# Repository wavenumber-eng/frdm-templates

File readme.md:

# FRDM MCX Templates

- Designs are now current edited in Altium, then imported into KiCad

- Always double check pin header IO assignments, mechanicals.  This template was created using the latest available documentation at the time of their creation. Reasonable efforts were made to ensure mechanical/electrical accuracy.   

- These templates are distributed in the hope that it will be useful, but WITHOUT ANY WARRANTY; without even the implied warranty of MERCHANTABILITY or FITNESS FOR A PARTICULAR PURPOSE.

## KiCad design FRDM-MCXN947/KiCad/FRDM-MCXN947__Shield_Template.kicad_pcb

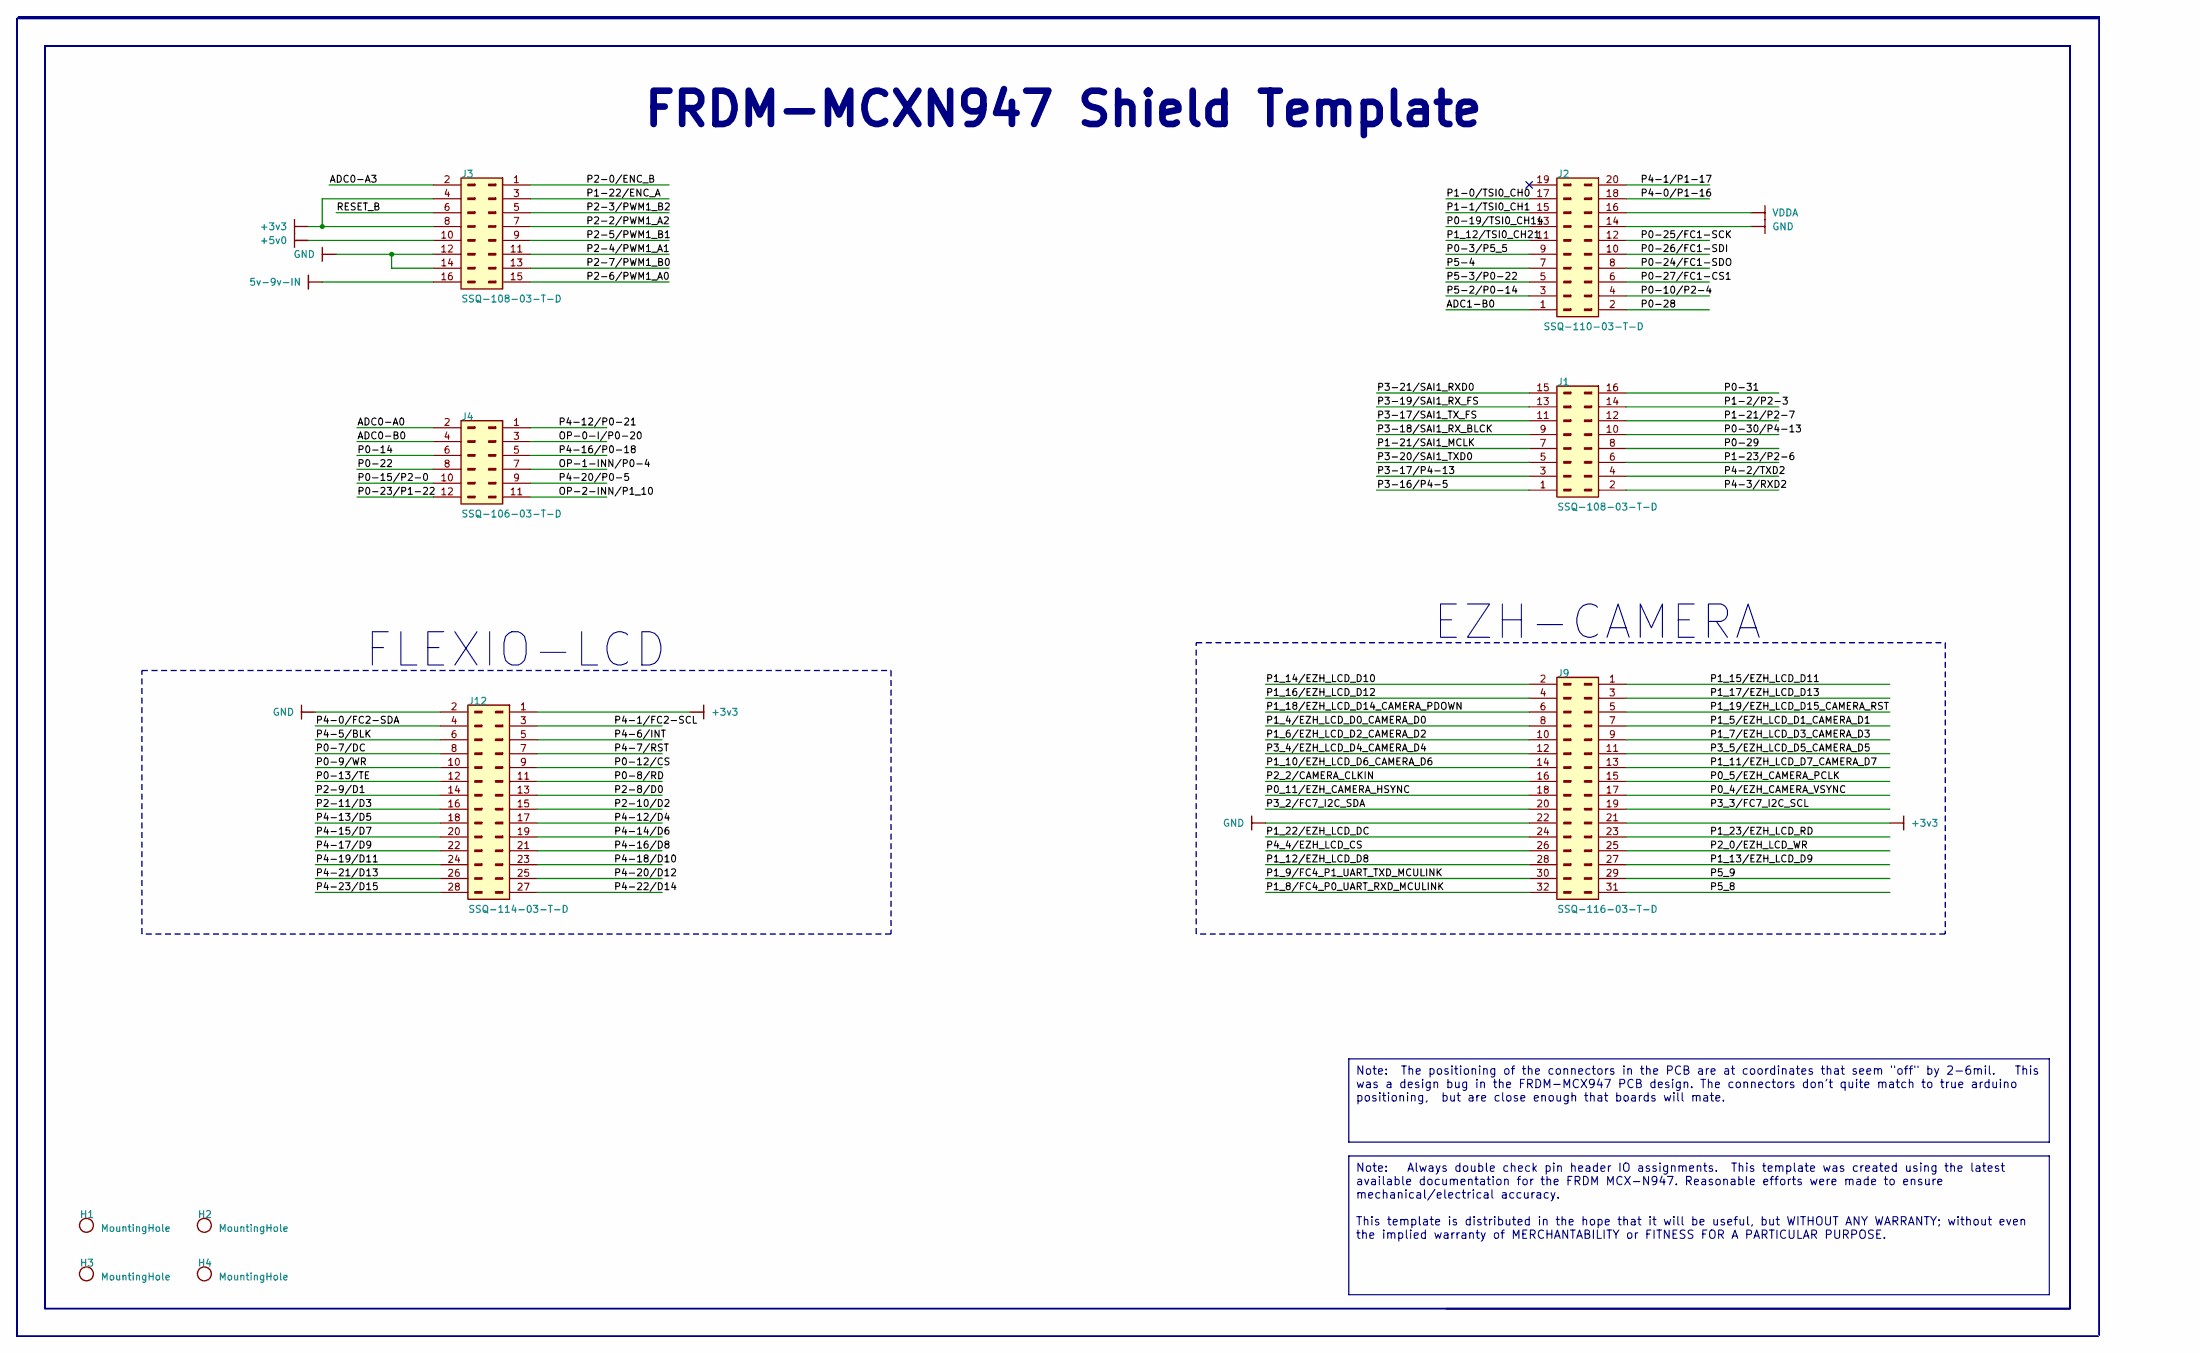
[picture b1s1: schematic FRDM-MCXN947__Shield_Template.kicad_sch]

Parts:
H1, H2, H3, H4: Mechanical_MountingHole; MountingHole_3.2mm_M3
J1, J3: SSQ-108-03-T-D; MANUFACTURER PART NUMBER SSQ-108-03-T-D
J2: SSQ-110-03-T-D; MANUFACTURER PART NUMBER SSQ-110-23-T-D
J4: SSQ-106-03-T-D; MANUFACTURER PART NUMBER SSQ-106-03-T-D
J9: SSQ-116-03-T-D; MANUFACTURER P/N SSQ-116-03-T-D
J12: SSQ-114-03-T-D; MANUFACTURER PART NUMBER SSQ-114-03-T-D

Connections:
5v-9v-IN: J3.16
+5v0: J3.10
ADC0-A0: J4.2
ADC0-A3: J3.2
ADC0-B0: J4.4
ADC1-B0: J2.1
OP-0-I/P0-20: J4.3
OP-1-INN/P0-4: J4.7
OP-2-INN/P1_10: J4.11
P0-3/P5_5: J2.9
P0-7/DC: J12.8
P0-8/RD: J12.11
P0-9/WR: J12.10
P0-10/P2-4: J2.4
P0-12/CS: J12.9
P0-13/TE: J12.12
P0-14: J4.6
P0-15/P2-0: J4.10
P0-19/TSI0_CH14: J2.13
P0-22: J4.8
P0-23/P1-22: J4.12
P0-24/FC1-SDO: J2.8
P0-25/FC1-SCK: J2.12
P0-26/FC1-SDI: J2.10
P0-27/FC1-CS1: J2.6
P0-28: J2.2
P0-29: J1.8
P0-30/P4-13: J1.10
P0-31: J1.16
P0_4/EZH_CAMERA_VSYNC: J9.17
P0_5/EZH_CAMERA_PCLK: J9.15
P0_11/EZH_CAMERA_HSYNC: J9.18
P1-0/TSI0_CH0: J2.17
P1-1/TSI0_CH1: J2.15
P1-2/P2-3: J1.14
P1-21/P2-7: J1.12
P1-21/SAI1_MCLK: J1.7
P1-22/ENC_A: J3.3
P1-23/P2-6: J1.6
P1_4/EZH_LCD_D0_CAMERA_D0: J9.8
P1_5/EZH_LCD_D1_CAMERA_D1: J9.7
P1_6/EZH_LCD_D2_CAMERA_D2: J9.10
P1_7/EZH_LCD_D3_CAMERA_D3: J9.9
P1_8/FC4_P0_UART_RXD_MCULINK: J9.32
P1_9/FC4_P1_UART_TXD_MCULINK: J9.30
P1_10/EZH_LCD_D6_CAMERA_D6: J9.14
P1_11/EZH_LCD_D7_CAMERA_D7: J9.13
P1_12/EZH_LCD_D8: J9.28
P1_12/TSI0_CH21: J2.11
P1_13/EZH_LCD_D9: J9.27
P1_14/EZH_LCD_D10: J9.2
P1_15/EZH_LCD_D11: J9.1
P1_16/EZH_LCD_D12: J9.4
P1_17/EZH_LCD_D13: J9.3
P1_18/EZH_LCD_D14_CAMERA_PDOWN: J9.6
P1_19/EZH_LCD_D15_CAMERA_RST: J9.5
P1_22/EZH_LCD_DC: J9.24
P1_23/EZH_LCD_RD: J9.23
P2-0/ENC_B: J3.1
P2-2/PWM1_A2: J3.7
P2-3/PWM1_B2: J3.5
P2-4/PWM1_A1: J3.11
P2-5/PWM1_B1: J3.9
P2-6/PWM1_A0: J3.15
P2-7/PWM1_B0: J3.13
P2-8/D0: J12.13
P2-9/D1: J12.14
P2-10/D2: J12.15
P2-11/D3: J12.16
P2_0/EZH_LCD_WR: J9.25
P2_2/CAMERA_CLKIN: J9.16
P3-16/P4-5: J1.1
P3-17/P4-13: J1.3
P3-17/SAI1_TX_FS: J1.11
P3-18/SAI1_RX_BLCK: J1.9
P3-19/SAI1_RX_FS: J1.13
P3-20/SAI1_TXD0: J1.5
P3-21/SAI1_RXD0: J1.15
P3_2/FC7_I2C_SDA: J9.20
P3_3/FC7_I2C_SCL: J9.19
P3_4/EZH_LCD_D4_CAMERA_D4: J9.12
P3_5/EZH_LCD_D5_CAMERA_D5: J9.11
P4-0/FC2-SDA: J12.4
P4-0/P1-16: J2.18
P4-1/FC2-SCL: J12.3
P4-1/P1-17: J2.20
P4-2/TXD2: J1.4
P4-3/RXD2: J1.2
P4-5/BLK: J12.6
P4-6/INT: J12.5
P4-7/RST: J12.7
P4-12/D4: J12.17
P4-12/P0-21: J4.1
P4-13/D5: J12.18
P4-14/D6: J12.19
P4-15/D7: J12.20
P4-16/D8: J12.21
P4-16/P0-18: J4.5
P4-17/D9: J12.22
P4-18/D10: J12.23
P4-19/D11: J12.24
P4-20/D12: J12.25
P4-20/P0-5: J4.9
P4-21/D13: J12.26
P4-22/D14: J12.27
P4-23/D15: J12.28
P4_4/EZH_LCD_CS: J9.26
P5-2/P0-14: J2.3
P5-3/P0-22: J2.5
P5-4: J2.7
P5_8: J9.31
P5_9: J9.29
RESET_B: J3.6
VDDA: J2.16

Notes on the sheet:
Note: Always double check pin header IO assignments. This template was created using the latest available documentation for the FRDM MCX-N947. Reasonable efforts were made to ensure mechanical/electrical accuracy. This template is distributed in the hope that it will be useful, but WITHOUT ANY WARR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
Note: The positioning of the connectors in the PCB are at coordinates that seem "off" by 2-6mil. This was a design bug in the FRDM-MCX947 PCB design. The connectors don't quite match to true arduino positioning, but are close enough that boards will mate.
FRDM-MCXN947 Shield Template
FLEXIO-LCD
EZH-CAMERA

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
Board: 2 copper layers, 10 parts (0 on the bottom side), 2 nets, no tracks yet.

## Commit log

2024-02-11 seeding
2024-02-11 minor text updates
2024-08-23 fixed bug in N947 template on J1. P0-29 and P1-23 were flopped
